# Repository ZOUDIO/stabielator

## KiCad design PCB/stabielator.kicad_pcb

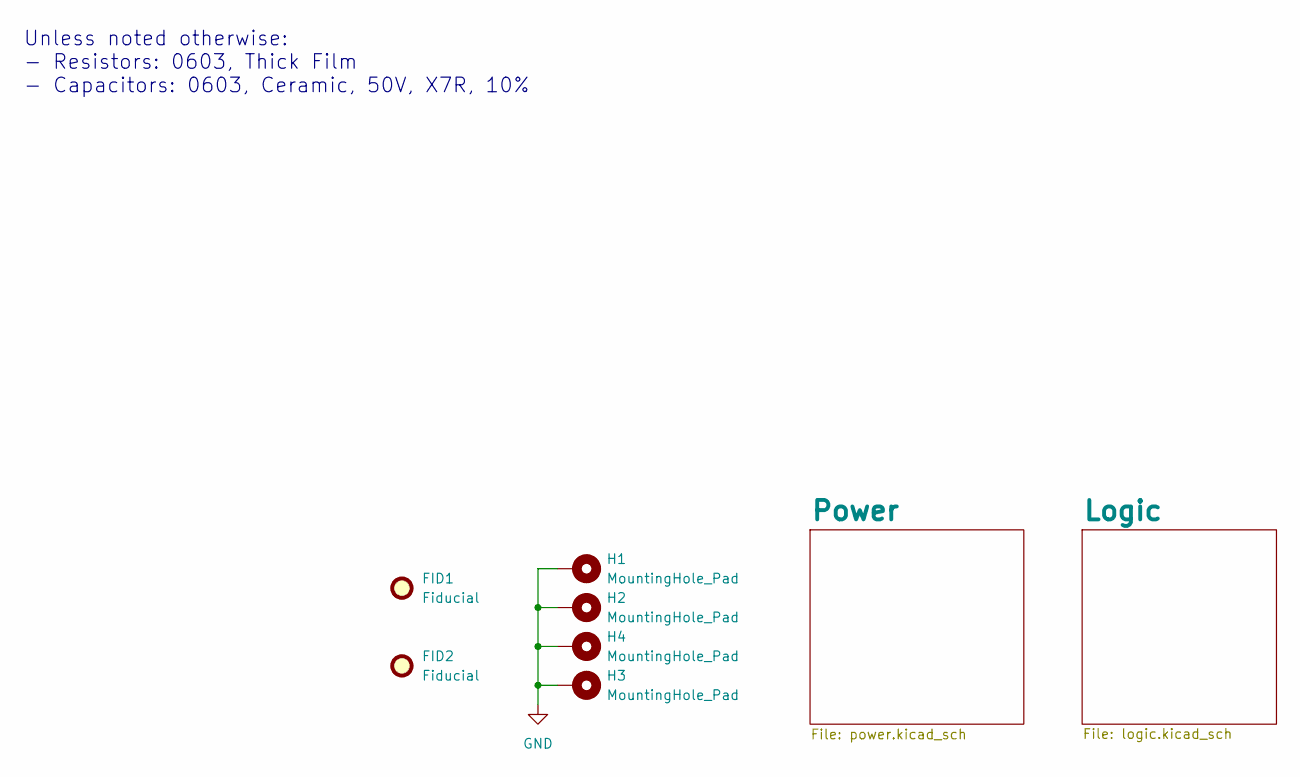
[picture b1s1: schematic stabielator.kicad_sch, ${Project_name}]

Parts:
FID1, FID2: Fiducial; Fiducial_0.5mm_Mask1mm
H1, H2, H3, H4: MountingHole_Pad; MountingHole_2.2mm_M2_Pad_Via; Digikey nvt

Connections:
GND: H1.1 (1_1), H2.1 (1_1), H3.1 (1_1), H4.1 (1_1); also elsewhere on the board

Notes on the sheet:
Unless noted otherwise: - Resistors: 0603, Thick Film - Capacitors: 0603, Ceramic, 50V, X7R, 10%

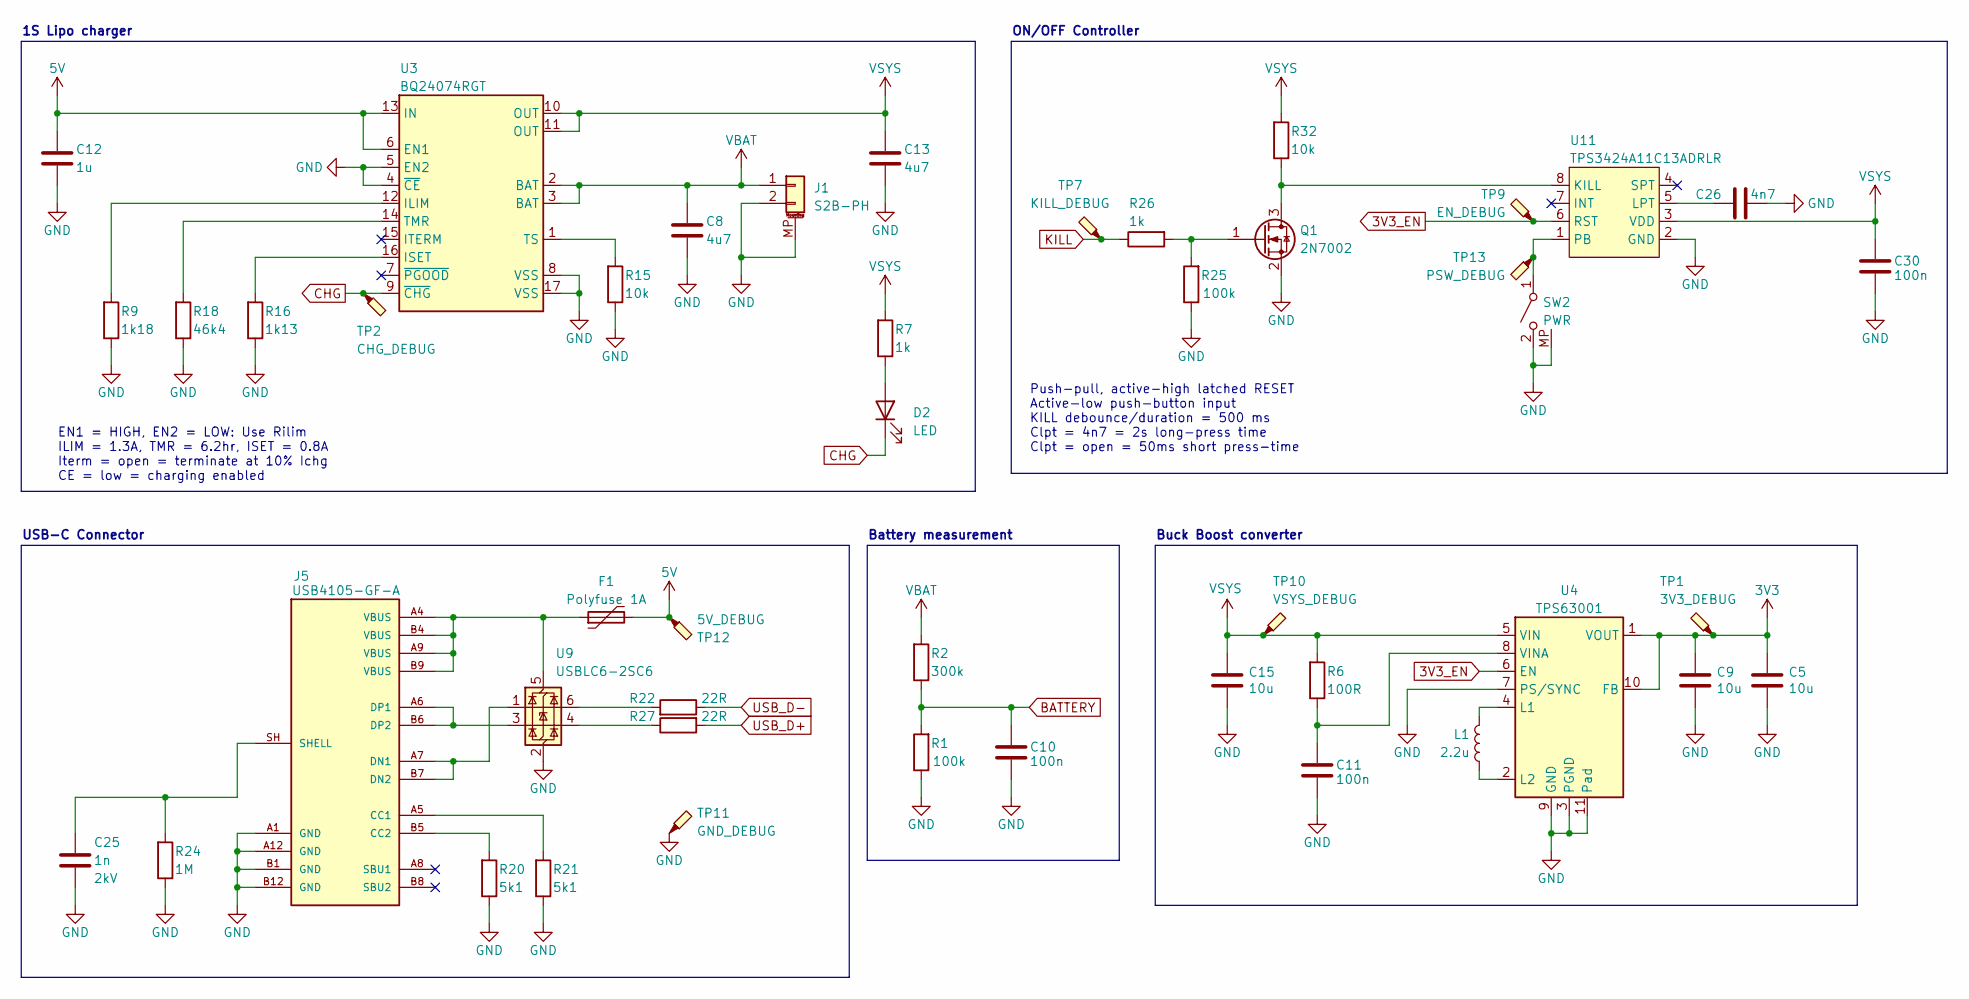
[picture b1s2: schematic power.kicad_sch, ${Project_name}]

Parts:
C5, C9, C15: 10u; C_1206_3216Metric; Partnumber CGA5L1X7R1C106K160AC; Digikey 445-12902-1-ND
C8, C13: 4u7; C_0805_2012Metric; Partnumber GRM21BR71C475KE51L; Digikey 490-14466-1-ND
C10, C11, C30: 100n; C_0603_1608Metric; Partnumber C0603C104K5RACTU; Digikey 399-C0603C104K5RACTUCT-ND
C12: 1u; C_0805_2012Metric; Partnumber GRM21BR71C105KA01L; Digikey 490-1691-1-ND
C25: 1n; C_1206_3216Metric; Voltage 2kV; Partnumber C1206C102KGRACTU; Digikey 399-C1206C102KGRACTUCT-ND
C26: 4n7; C_0603_1608Metric; Partnumber C1608X7R1H472K080AE; Digikey 445-173690-1-ND
D2: LED; LED_0603_1608Metric; Partnumber 150060RS55040; Digikey 732-12015-1-ND
F1: Polyfuse 1A; Fuse_0805_2012Metric; Partnumber 0ZCK0100FF2E; Digikey 5923-0ZCK0100FF2ECT-ND
J1: S2B-PH; JST_PH_S2B-PH-SM4-TB_1x02-1MP_P2.00mm_Horizontal; Partnumber S2B-PH-SM4-TB; Digikey 455-S2B-PH-SM4-TBCT-ND
J5: USB4105-GF-A; USB_C_Receptacle_Palconn_UTC16-G; Partnumber USB4105-GF-A; Digikey 2073-USB4105-GF-ACT-ND
L1: 2.2u; L_Bourns-SRN4018; Partnumber SRN4018-2R2M; Digikey SRN4018-2R2MCT-ND
Q1: 2N7002; SOT-23; Partnumber 2N7002; Digikey 2N7002NCT-ND
R1, R25: 100k; R_0603_1608Metric; Partnumber RC0603FR-07100KL; Digikey 311-100KHRCT-ND
R2: 300k; R_0603_1608Metric; Partnumber RC0603FR-07300KL; Digikey 311-300KHRTR-ND
R6: 100R; R_0603_1608Metric; Partnumber RC0603FR-07100RL; Digikey 311-100HRCT-ND
R7, R26: 1k; R_0603_1608Metric; Partnumber RC0603FR-071KL; Digikey 311-1.00KHRCT-ND
R9: 1k18; R_0603_1608Metric; Partnumber RC0603FR-071K18L; Digikey 311-1.18KHRCT-ND
R15, R32: 10k; R_0603_1608Metric; Partnumber RC0603FR-0710KL; Digikey 311-10.0KHRCT-ND
R16: 1k13; R_0603_1608Metric; Partnumber RC0603FR-071K13L; Digikey 311-1.13KHRCT-ND
R18: 46k4; R_0603_1608Metric; Partnumber RC0603FR-0746K4L; Digikey 311-46.4KHRCT-ND
R20, R21: 5k1; R_0603_1608Metric; Partnumber RC0603FR-075K1L; Digikey 311-5.10KHRTR-ND
R22, R27: 22R; R_0603_1608Metric; Partnumber RC0603FR-0722RL; Digikey 311-22.0HRTR-ND
R24: 1M; R_0603_1608Metric; Partnumber RC0603FR-071ML; Digikey 311-1.00MHRCT-ND
SW2: PWR; SW_Push_1P1T-MP_NO_Horizontal_Alps_SKRTLAE010; Partnumber SKRTLAE010; Digikey 4809-SKRTLAE010CT-ND
TP1: 3V3_DEBUG; TestPoint_Pad_D1.0mm; Digikey nvt
TP2: CHG_DEBUG; TestPoint_Pad_D1.0mm; Digikey nvt
TP7: KILL_DEBUG; TestPoint_Pad_D1.0mm; Digikey nvt
TP9: EN_DEBUG; TestPoint_Pad_D1.0mm; Digikey nvt
TP10: VSYS_DEBUG; TestPoint_Pad_D1.0mm; Digikey nvt
TP11: GND_DEBUG; TestPoint_Pad_D1.0mm; Digikey nvt
TP12: 5V_DEBUG; TestPoint_Pad_D1.0mm; Digikey nvt
TP13: PSW_DEBUG; TestPoint_Pad_D1.0mm; Digikey nvt
U3: BQ24074RGT; VQFN-16-1EP_3x3mm_P0.5mm_EP1.6x1.6mm_ThermalVias; Partnumber BQ24074RGTR; Digikey 296-38873-1-ND
U4: TPS63001; Texas_DRC0010J_ThermalVias; Partnumber TPS63001DRCR; Digikey 296-19643-1-ND
U9: USBLC6-2SC6; SOT-23-6; Partnumber USBLC6-2SC6; Digikey 497-5235-2-ND
U11: TPS3424A11C13ADRLR; SOT-583-8; Partnumber TPS3424A11C13ADRLR; Digikey 296-TPS3424A11C13ADRLRCT-ND

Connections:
3V3: C5.1, C9.1, TP1.1 (1_1), U4.1 (VOUT), U4.10 (FB); also elsewhere on the board
3V3_EN: TP9.1 (1_1), U4.6 (EN), U11.6 (RST)
5V: C12.1, F1.2, TP12.1 (1_1), U3.6 (EN1), U3.13 (IN)
BATTERY: C10.1, R1.1, R2.2; also elsewhere on the board
CHG: D2.1 (K), TP2.1 (1_1), U3.9 (~CHG)
GND: C5.2, C8.2, C9.2, C10.2, C11.2, C12.2, C13.2, C15.2, C25.2, C26.2, C30.2, J1.2, J1.MP (MountPin), J5.A1 (GND), J5.A12 (GND), J5.B1 (GND), J5.B12 (GND), Q1.2 (S), R1.2, R9.2, R15.2, R16.2, R18.2, R20.2, R21.2, R24.2, R25.2, SW2.2 (B), SW2.MP, TP11.1 (1_1), U3.4 (~CE), U3.5 (EN2), U3.8 (VSS), U3.17 (VSS), U4.3 (PGND), U4.7 (PS/SYNC), U4.9 (GND), U4.11 (PGND), U9.2 (GND), U11.2 (GND); also elsewhere on the board
KILL: R26.2, TP7.1 (1_1); also elsewhere on the board
unnamed: D2.2 (A), R7.2
unnamed: J5.A5 (CC1), R21.1
unnamed: J5.B5 (CC2), R20.1
unnamed: J5.A7 (DN1), J5.B7 (DN2), U9.1 (I/O1)
unnamed: J5.A6 (DP1), J5.B6 (DP2), U9.3 (I/O2)
unnamed: C25.1, J5.SH (SHELL), R24.1
unnamed: Q1.3 (D), R32.2, U11.8 (KILL)
unnamed: Q1.1 (G), R25.1, R26.1
unnamed: R22.1, U9.6 (I/O1)
unnamed: R27.2, U9.4 (I/O2)
unnamed: SW2.1 (A), TP13.1 (1_1), U11.1 (PB)
unnamed: R9.1, U3.12 (ILIM)
unnamed: R16.1, U3.16 (ISET)
unnamed: R18.1, U3.14 (TMR)
unnamed: R15.1, U3.1 (TS)
unnamed: L1.1, U4.4 (L1)
unnamed: L1.2, U4.2 (L2)
unnamed: C11.1, R6.2, U4.8 (VINA)
unnamed: F1.1, J5.A4 (VBUS), J5.A9 (VBUS), J5.B4 (VBUS), J5.B9 (VBUS), U9.5 (VBUS)
unnamed: C26.1, U11.5 (LPT)
USB_D+: R27.1; also elsewhere on the board
USB_D-: R22.2; also elsewhere on the board
VBAT: C8.1, J1.1, R2.1, U3.2 (BAT), U3.3 (BAT)
VSYS: C13.1, C15.1, C30.1, R6.1, R7.1, R32.1, TP10.1 (1_1), U3.10 (OUT), U3.11 (OUT), U4.5 (VIN), U11.3 (VDD)

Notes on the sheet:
1S Lipo charger
USB-C Connector
Buck Boost converter
Push-pull, active-high latched RESET Active-low push-button input KILL debounce/duration = 500 ms Clpt = 4n7 = 2s long-press time Clpt = open = 50ms short press-time
EN1 = HIGH, EN2 = LOW: Use Rilim ILIM = 1.3A, TMR = 6.2hr, ISET = 0.8A Iterm = open = terminate at 10% Ichg CE = low = charging enabled
Battery measurement
ON/OFF Controller

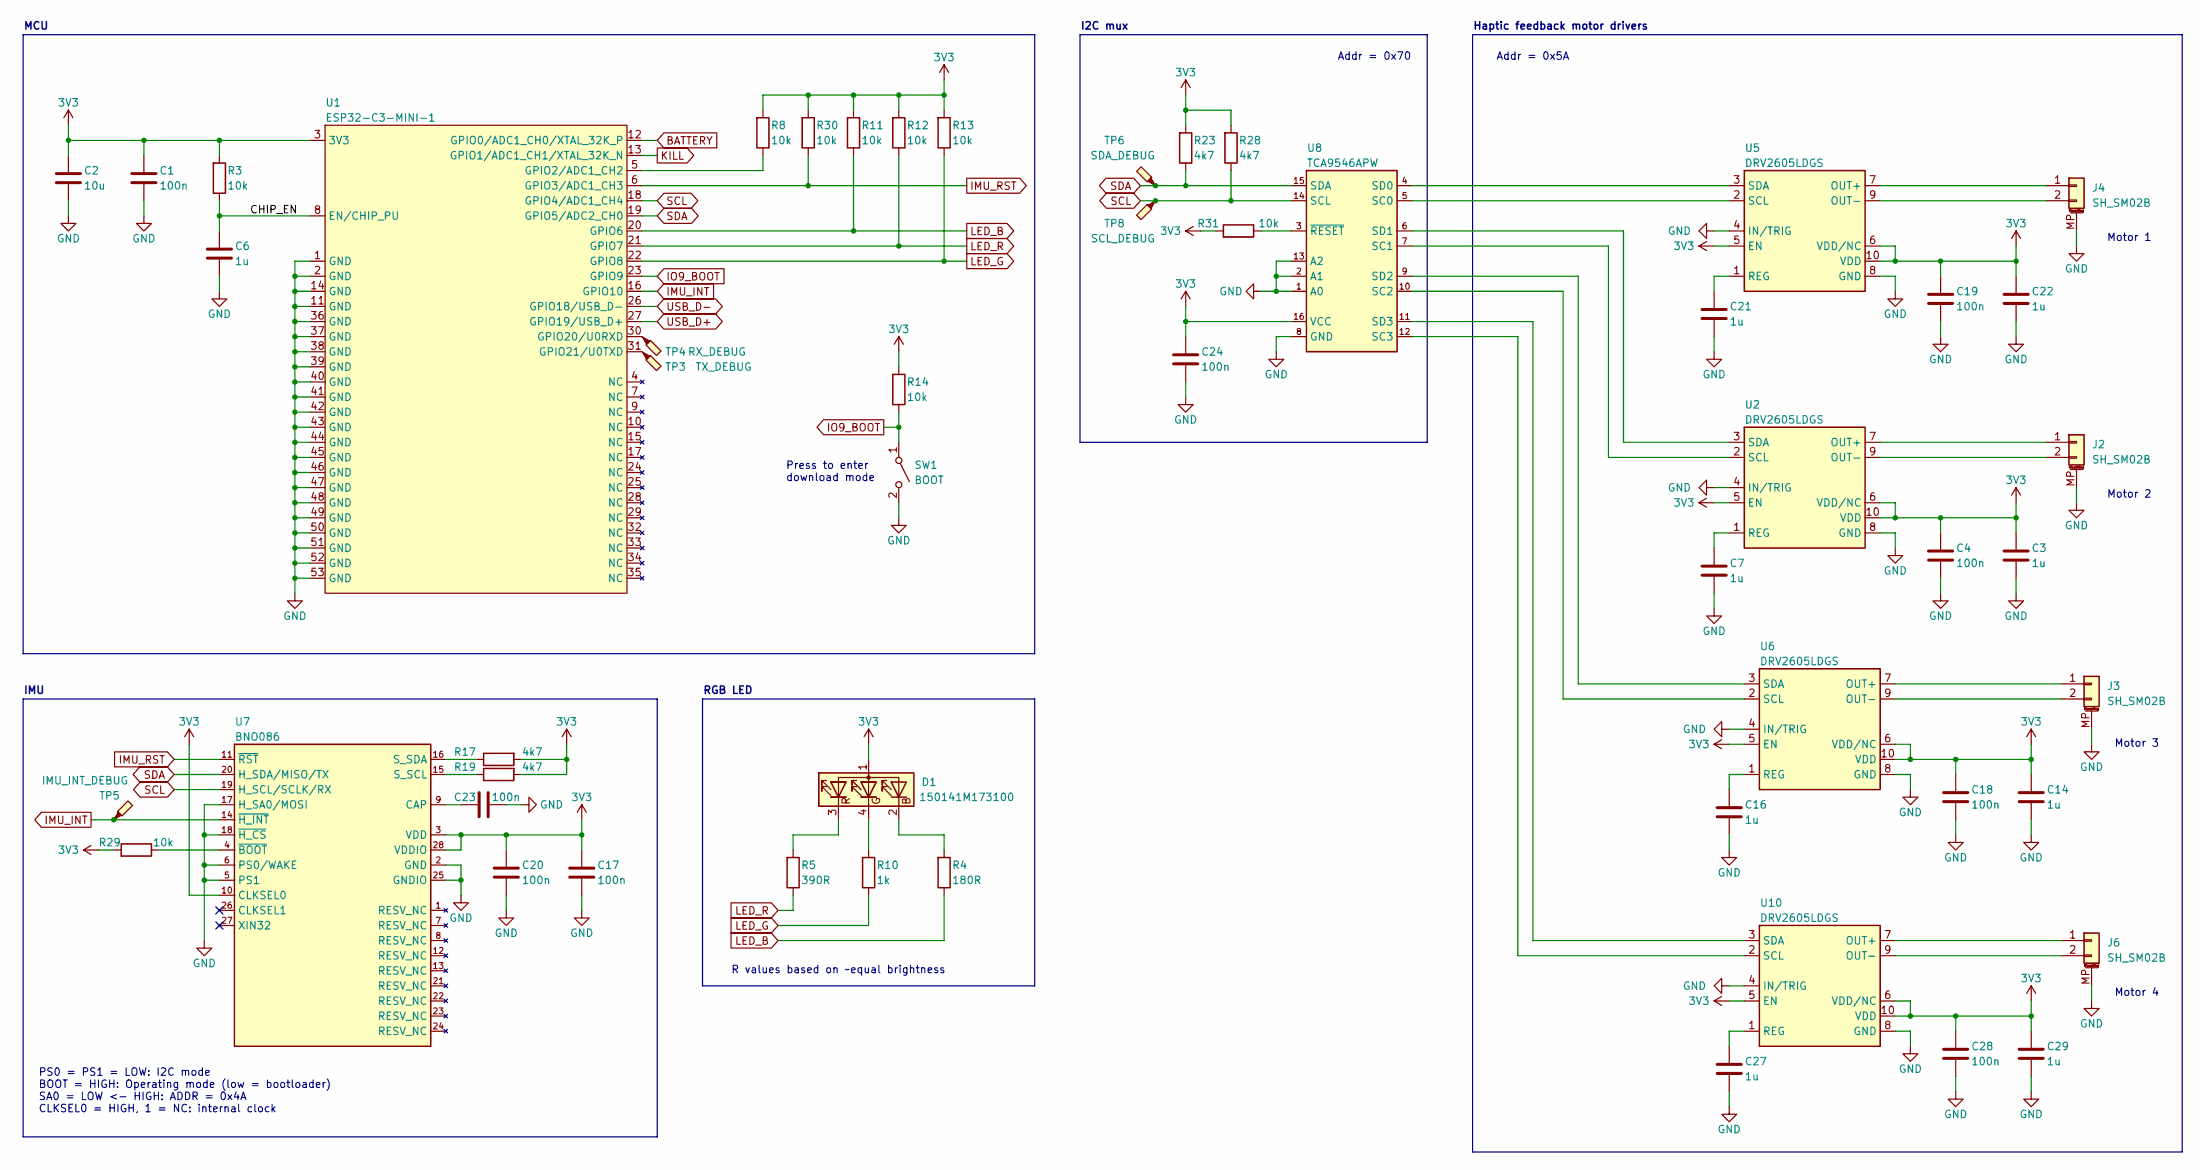
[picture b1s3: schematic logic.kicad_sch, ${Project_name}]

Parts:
C1, C4, C17, C18, C19, C20, C23, C24, C28: 100n; C_0603_1608Metric; Partnumber C0603C104K5RACTU; Digikey 399-C0603C104K5RACTUCT-ND
C2: 10u; C_0805_2012Metric; Partnumber CL21B106KOQNNNE; Digikey 1276-2872-1-ND
C3, C6, C7, C14, C16, C21, C22, C27, C29: 1u; C_0603_1608Metric; Partnumber C1608X7R1C105K080AC; Digikey 445-1604-1-ND
D1: 150141M173100; LED_RGB_Wuerth-PLCC4_3.2x2.8mm_150141M173100; Partnumber 150141M173100; Digikey 732-4998-1-ND
J2, J3, J4, J6: SH_SM02B; JST_SH_SM02B-SRSS-TB_1x02-1MP_P1.00mm_Horizontal; Partnumber SM02B-SRSS-TB; Digikey 455-SM02B-SRSS-TBCT-ND
R3, R8, R11, R12, R13, R14, R29, R30, R31: 10k; R_0603_1608Metric; Partnumber RC0603FR-0710KL; Digikey 311-10.0KHRCT-ND
R4: 180R; R_0603_1608Metric; Partnumber RC0603FR-07180RL; Digikey 311-180HRCT-ND
R5: 390R; R_0603_1608Metric; Partnumber RC0603FR-07390RL; Digikey 311-390HRCT-ND
R10: 1k; R_0603_1608Metric; Partnumber RC0603FR-071KL; Digikey 311-1.00KHRCT-ND
R17, R19, R23, R28: 4k7; R_0603_1608Metric; Partnumber RC0603FR-074K7L; Digikey 311-4.70KHRCT-ND
SW1: BOOT; SW_SPST_B3U-1000P; Partnumber B3U-1000P; Digikey SW1020CT-ND
TP3: TX_DEBUG; TestPoint_Pad_D1.0mm; Digikey nvt
TP4: RX_DEBUG; TestPoint_Pad_D1.0mm; Digikey nvt
TP5: IMU_INT_DEBUG; TestPoint_Pad_D1.0mm; Digikey nvt
TP6: SDA_DEBUG; TestPoint_Pad_D1.0mm; Digikey nvt
TP8: SCL_DEBUG; TestPoint_Pad_D1.0mm; Digikey nvt
U1: ESP32-C3-MINI-1; Partnumber ESP32-C3-MINI-1-N4; Digikey 5407-ESP32-C3-MINI-1-N4CT-ND
U2, U5, U6, U10: DRV2605LDGS; TSSOP-10_3x3mm_P0.5mm; Partnumber DRV2605LDGSR; Digikey 296-40032-1-ND
U7: BNO086; LGA-28; Partnumber BNO086; Digikey 1888-BNO086CT-ND
U8: TCA9546APW; TSSOP-16_4.4x5mm_P0.65mm; Partnumber TCA9546APWR; Digikey 4518-TCA9546APWRCT-ND

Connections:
3V3: C1.1, C2.1, C3.1, C4.1, C14.1, C17.1, C18.1, C19.1, C20.1, C22.1, C24.1, C28.1, C29.1, D1.1 (A), R3.1, R8.1, R11.1, R12.1, R13.1, R14.1, R17.1, R19.1, R23.1, R28.1, R29.1, R30.1, R31.1, U1.3 (3V3), U2.5 (EN), U2.6 (VDD/NC), U2.10 (VDD), U5.5 (EN), U5.6 (VDD/NC), U5.10 (VDD), U6.5 (EN), U6.6 (VDD/NC), U6.10 (VDD), U7.3 (VDD), U7.10 (CLKSEL0), U7.28 (VDDIO), U8.16 (VCC), U10.5 (EN), U10.6 (VDD/NC), U10.10 (VDD); also elsewhere on the board
/Logic/CHIP_EN: C6.1, R3.2, U1.8 (EN/CHIP_PU)
BATTERY: U1.12 (GPIO0/ADC1_CH0/XTAL_32K_P); also elsewhere on the board
GND: C1.2, C2.2, C3.2, C4.2, C6.2, C7.2, C14.2, C16.2, C17.2, C18.2, C19.2, C20.2, C21.2, C22.2, C23.1, C24.2, C27.2, C28.2, C29.2, J2.MP (MountPin), J3.MP (MountPin), J4.MP (MountPin), J6.MP (MountPin), SW1.2 (B), U1.1 (GND), U1.2 (GND), U1.11 (GND), U1.14 (GND), U1.36 (GND), U1.37 (GND), U1.38 (GND), U1.39 (GND), U1.40 (GND), U1.41 (GND), U1.42 (GND), U1.43 (GND), U1.44 (GND), U1.45 (GND), U1.46 (GND), U1.47 (GND), U1.48 (GND), U1.49 (GND), U1.50 (GND), U1.51 (GND), U1.52 (GND), U1.53 (GND), U2.4 (IN/TRIG), U2.8 (GND), U5.4 (IN/TRIG), U5.8 (GND), U6.4 (IN/TRIG), U6.8 (GND), U7.2 (GND), U7.5 (PS1), U7.6 (PS0/WAKE), U7.17 (H_SA0/MOSI), U7.18 (~H_CS), U7.25 (GNDIO), U8.1 (A0), U8.2 (A1), U8.8 (GND), U8.13 (A2), U10.4 (IN/TRIG), U10.8 (GND); also elsewhere on the board
IMU_INT: TP5.1 (1_1), U1.16 (GPIO10), U7.14 (~H_INT)
IMU_RST: R30.2, U1.6 (GPIO3/ADC1_CH3), U7.11 (~RST)
IO9_BOOT: R14.2, SW1.1 (A), U1.23 (GPIO9)
KILL: U1.13 (GPIO1/ADC1_CH1/XTAL_32K_N); also elsewhere on the board
LED_B: R4.2, R11.2, U1.20 (GPIO6)
LED_G: R10.2, R13.2, U1.22 (GPIO8)
LED_R: R5.2, R12.2, U1.21 (GPIO7)
unnamed: D1.2 (BK), R4.1
unnamed: D1.4 (GK), R10.1
unnamed: D1.3 (RK), R5.1
unnamed: J2.1, U2.7 (OUT+)
unnamed: J2.2, U2.9 (OUT-)
unnamed: J3.1, U6.7 (OUT+)
unnamed: J3.2, U6.9 (OUT-)
unnamed: J4.1, U5.7 (OUT+)
unnamed: J4.2, U5.9 (OUT-)
unnamed: J6.1, U10.7 (OUT+)
unnamed: J6.2, U10.9 (OUT-)
unnamed: R8.2, U1.5 (GPIO2/ADC1_CH2)
unnamed: TP4.1 (1_1), U1.30 (GPIO20/U0RXD)
unnamed: TP3.1 (1_1), U1.31 (GPIO21/U0TXD)
unnamed: C7.1, U2.1 (REG)
unnamed: U2.2 (SCL), U8.7 (SC1)
unnamed: U2.3 (SDA), U8.6 (SD1)
unnamed: C21.1, U5.1 (REG)
unnamed: U5.2 (SCL), U8.5 (SC0)
unnamed: U5.3 (SDA), U8.4 (SD0)
unnamed: C16.1, U6.1 (REG)
unnamed: U6.2 (SCL), U8.10 (SC2)
unnamed: U6.3 (SDA), U8.9 (SD2)
unnamed: C23.2, U7.9 (CAP)
unnamed: R19.2, U7.15 (S_SCL)
unnamed: R17.2, U7.16 (S_SDA)
unnamed: R29.2, U7.4 (~BOOT)
unnamed: R31.2, U8.3 (~RESET)
unnamed: C27.1, U10.1 (REG)
unnamed: U8.12 (SC3), U10.2 (SCL)
unnamed: U8.11 (SD3), U10.3 (SDA)
SCL: R28.2, TP8.1 (1_1), U1.18 (GPIO4/ADC1_CH4), U7.19 (H_SCL/SCLK/RX), U8.14 (SCL)
SDA: R23.2, TP6.1 (1_1), U1.19 (GPIO5/ADC2_CH0), U7.20 (H_SDA/MISO/TX), U8.15 (SDA)
USB_D+: U1.27 (GPIO19/USB_D+); also elsewhere on the board
USB_D-: U1.26 (GPIO18/USB_D-); also elsewhere on the board

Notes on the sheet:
I2C mux
IMU
MCU
Haptic feedback motor drivers
Addr = 0x70
Motor 3
PS0 = PS1 = LOW: I2C mode BOOT = HIGH: Operating mode (low = bootloader) SA0 = LOW <- HIGH: ADDR = 0x4A CLKSEL0 = HIGH, 1 = NC: internal clock
RGB LED
Motor 2
Press to enter download mode
R values based on ~equal brightness
Addr = 0x5A
Motor 1
Motor 4

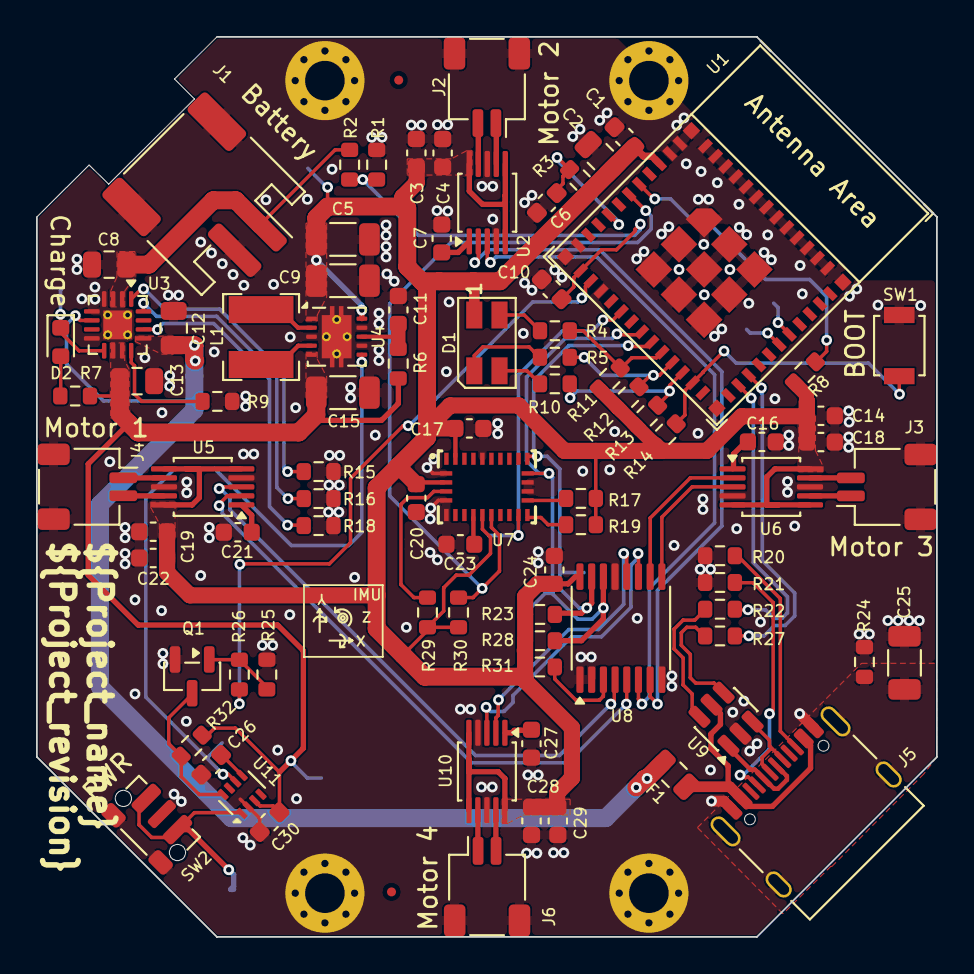
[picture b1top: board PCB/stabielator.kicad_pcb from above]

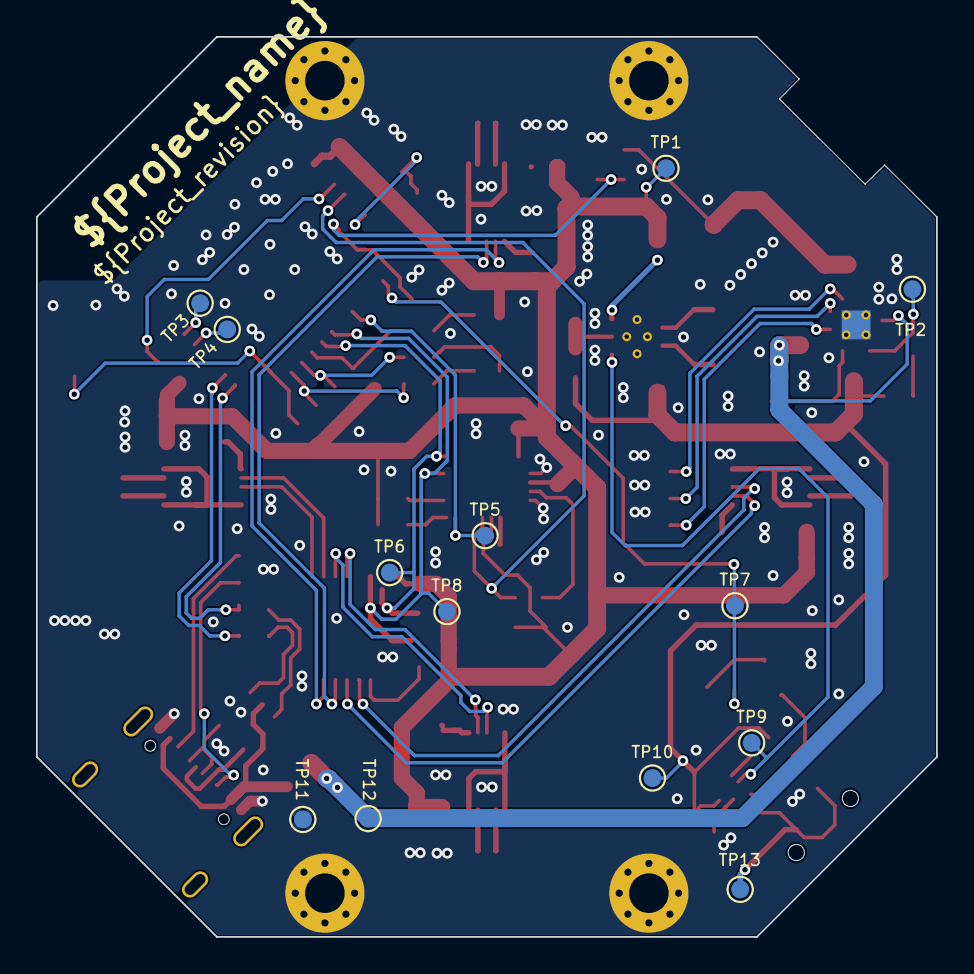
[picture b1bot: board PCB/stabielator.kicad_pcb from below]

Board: 4 copper layers, 50.0 x 50.0 mm, 106 parts (13 on the bottom side), 71 nets.

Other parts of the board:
SYM1: IMU_XYZ_Orientation

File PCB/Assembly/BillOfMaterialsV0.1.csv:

"Reference","Qty","Value","Footprint","Digikey"
"C1,C4,C10,C11,C17,C18,C19,C20,C23,C24,C28,C30","12","100n","Capacitor_SMD:C_0603_1608Metric","399-C0603C104K5RACTUCT-ND"
"C2","1","10u","Capacitor_SMD:C_0805_2012Metric","1276-2872-1-ND"
"C3,C6,C7,C14,C16,C21,C22,C27,C29","9","1u","Capacitor_SMD:C_0603_1608Metric","445-1604-1-ND"
"C5,C9,C15","3","10u","Capacitor_SMD:C_1206_3216Metric","445-12902-1-ND"
"C8,C13","2","4u7","Capacitor_SMD:C_0805_2012Metric","490-14466-1-ND"
"C12","1","1u","Capacitor_SMD:C_0805_2012Metric","490-1691-1-ND"
"C25","1","1n","Capacitor_SMD:C_1206_3216Metric","399-C1206C102KGRACTUCT-ND"
"C26","1","4n7","Capacitor_SMD:C_0603_1608Metric","445-173690-1-ND"
"D1","1","150141M173100","LED_SMD:LED_RGB_Wuerth-PLCC4_3.2x2.8mm_150141M173100","732-4998-1-ND"
"D2","1","LED","LED_SMD:LED_0603_1608Metric","732-12015-1-ND"
"F1","1","Polyfuse 1A","Fuse:Fuse_0805_2012Metric","5923-0ZCK0100FF2ECT-ND"
"J1","1","S2B-PH","Connector_JST:JST_PH_S2B-PH-SM4-TB_1x02-1MP_P2.00mm_Horizontal","455-S2B-PH-SM4-TBCT-ND"
"J2,J3,J4,J6","4","SH_SM02B","Connector_JST:JST_SH_SM02B-SRSS-TB_1x02-1MP_P1.00mm_Horizontal","455-SM02B-SRSS-TBCT-ND"
"J5","1","USB4105-GF-A","Connector_USB:USB_C_Receptacle_Palconn_UTC16-G","2073-USB4105-GF-ACT-ND"
"L1","1","2.2u","Inductor_SMD:L_Bourns-SRN4018","SRN4018-2R2MCT-ND"
"Q1","1","2N7002","Package_TO_SOT_SMD:SOT-23","2N7002NCT-ND"
"R1","1","100k 0.1%","Resistor_SMD:R_0603_1608Metric","YAG1235CT-ND"
"R2","1","300k 0.1%","Resistor_SMD:R_0603_1608Metric","YAG1627CT-ND"
"R3,R8,R11,R12,R13,R14,R15,R29,R30,R31,R32","11","10k","Resistor_SMD:R_0603_1608Metric","311-10.0KHRCT-ND"
"R4","1","180R","Resistor_SMD:R_0603_1608Metric","311-180HRCT-ND"
"R5","1","390R","Resistor_SMD:R_0603_1608Metric","311-390HRCT-ND"
"R6","1","100R","Resistor_SMD:R_0603_1608Metric","311-100HRCT-ND"
"R7,R10,R26","3","1k","Resistor_SMD:R_0603_1608Metric","311-1.00KHRCT-ND"
"R9","1","1k18","Resistor_SMD:R_0603_1608Metric","311-1.18KHRCT-ND"
"R16","1","1k13","Resistor_SMD:R_0603_1608Metric","311-1.13KHRCT-ND"
"R17,R19,R23,R28","4","4k7","Resistor_SMD:R_0603_1608Metric","311-4.70KHRCT-ND"
"R18","1","46k4","Resistor_SMD:R_0603_1608Metric","311-46.4KHRCT-ND"
"R20,R21","2","5k1","Resistor_SMD:R_0603_1608Metric","YAG3621CT-ND"
"R22,R27","2","22R","Resistor_SMD:R_0603_1608Metric","YAG3581CT-ND"
"R24","1","1M","Resistor_SMD:R_0603_1608Metric","311-1.00MHRCT-ND"
"R25","1","100k","Resistor_SMD:R_0603_1608Metric","311-100KHRCT-ND"
"SW1","1","BOOT","Button_Switch_SMD:SW_SPST_B3U-1000P","SW1020CT-ND"
"SW2","1","PWR","Button_Switch_SMD:SW_Push_1P1T-MP_NO_Horizontal_Alps_SKRTLAE010","4809-SKRTLAE010CT-ND"
"U1","1","ESP32-C3-MINI-1","PCM_Espressif:ESP32-C3-MINI-1","5407-ESP32-C3-MINI-1-N4CT-ND"
"U2,U5,U6,U10","4","DRV2605LDGS","Package_SO:TSSOP-10_3x3mm_P0.5mm","296-40032-1-ND"
"U3","1","BQ24074RGT","Package_DFN_QFN:VQFN-16-1EP_3x3mm_P0.5mm_EP1.6x1.6mm_ThermalVias","296-38873-1-ND"
"U4","1","TPS63001","Package_SON:Texas_DRC0010J_ThermalVias","296-19643-1-ND"
"U7","1","BNO086","stabielator:LGA-28","1888-BNO086CT-ND"
"U8","1","TCA9546APW","Package_SO:TSSOP-16_4.4x5mm_P0.65mm","4518-TCA9546APWRCT-ND"
"U9","1","USBLC6-2SC6","Package_TO_SOT_SMD:SOT-23-6","5399-USBLC6-2SC6CT-ND"
"U11","1","TPS3424A11C13ADRLR","Package_TO_SOT_SMD:SOT-583-8","296-TPS3424A11C13ADRLRCT-ND"

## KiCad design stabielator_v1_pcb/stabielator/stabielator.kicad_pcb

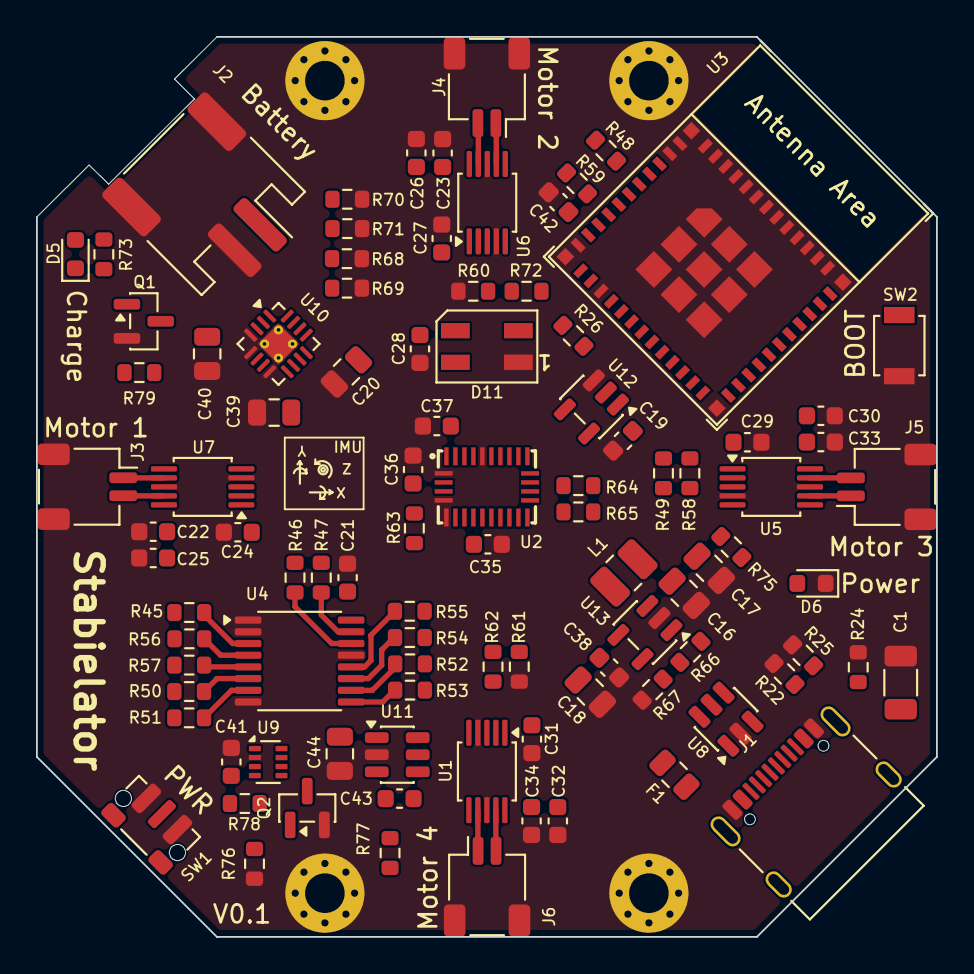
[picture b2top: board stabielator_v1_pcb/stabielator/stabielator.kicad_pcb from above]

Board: 2 copper layers, 50.0 x 50.0 mm, 100 parts (0 on the bottom side), 68 nets.

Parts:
C1: 1n-2kV; C_1206_3216Metric
C16, C17, C18: 22uF; C_0805_2012Metric
C19, C21, C22, C23, C28, C33, C34, C35, C36, C37, C38, C41: 100nF; C_0603_1608Metric
C20, C44: 1uF; C_0805_2012Metric
C24, C25, C26, C27, C29, C30, C31, C32: 1uF; C_0603_1608Metric
C39, C40: 4.7uF; C_0805_2012Metric
C42: 1U; C_0603_1608Metric
C43: 1nF; C_0603_1608Metric
D5: LED_R; LED_0603_1608Metric
D6: LED_G; LED_0603_1608Metric
D11: SK6812; LED_SK6812MINI_PLCC4_3.5x3.5mm_P1.75mm
F1: Polyfuse 1A; Fuse_0805_2012Metric
H1, H2, H3, H4: MountingHole_Pad; MountingHole_2.2mm_M2_Pad_Via
J1: USB_C_Receptacle_USB2.0_16P; USB_C_Receptacle_Palconn_UTC16-G
J2: Battery; JST_PH_S2B-PH-SM4-TB_1x02-1MP_P2.00mm_Horizontal
J3: Motor 1; JST_SH_SM02B-SRSS-TB_1x02-1MP_P1.00mm_Horizontal
J4: Motor 2; JST_SH_SM02B-SRSS-TB_1x02-1MP_P1.00mm_Horizontal
J5: Motor 3; JST_SH_SM02B-SRSS-TB_1x02-1MP_P1.00mm_Horizontal
J6: Motor 4; JST_SH_SM02B-SRSS-TB_1x02-1MP_P1.00mm_Horizontal
L1: 2.2uH; L_1008_2520Metric
Q1, Q2: 2N7002; SOT-23
R22, R25: 5k1; R_0603_1608Metric
R24: 1M; R_0603_1608Metric
R26: 330R; R_0603_1608Metric
R45, R48, R49, R58, R59, R60, R61, R62, R63, R71, R72, R78: 10K; R_0603_1608Metric
R46, R47, R50, R51, R52, R53, R54, R55, R56, R57, R64, R65: 4K7; R_0603_1608Metric
R66: 453K; R_0603_1608Metric
R67, R76, R79: 100K; R_0603_1608Metric
R68: 46.4K; R_0603_1608Metric
R69: 1.13K; R_0603_1608Metric
R70: 1.18K; R_0603_1608Metric
R73, R75, R77: 1K; R_0603_1608Metric
SW1: PWR; SW_Push_1P1T-MP_NO_Horizontal_Alps_SKRTLAE010
SW2: BOOT; SW_SPST_B3U-1000P
U1, U5, U6, U7: DRV2605LDGS; TSSOP-10_3x3mm_P0.5mm
U2: LGA-28
U3: ESP32-C3-MINI-1
U4: TCA9546APW; TSSOP-16_4.4x5mm_P0.65mm
U8: USBLC6-2SC6; SOT-23-6
U9: TPS3424A11C13ADRLR; SOT-583-8
U10: BQ24074RGT; VQFN-16-1EP_3x3mm_P0.5mm_EP1.6x1.6mm_ThermalVias
U11: TPS22917DBV; SOT-23-6
U12: 74AHCT1G126; SOT-23-5
U13: TLV62569DBV; SOT-23-5

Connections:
3V3: C16.2, C17.2, C36.2, C37.2, L1.2, R48.1, R49.1, R58.1, R59.1, R63.2, R64.1, R65.1, R66.1, R72.1, R75.1, U2.3 (VDD), U2.10 (CLKSEL0), U2.28 (VDDIO), U3.3 (3V3)
5V: C20.2, F1.2, U10.6 (EN1), U10.13 (IN)
+3.3V: C21.2, R45.1, R46.1, R47.1, U4.16 (VCC)
+BATT: C40.2, J2.1, U10.2 (BAT), U10.3 (BAT)
/CHIP_EN: C42.1, R59.2, U3.8 (EN/CHIP_PU)
BATTERY: R61.1, R62.2, U3.6 (GPIO3/ADC1_CH3)
BATT_VCC: C39.2, C41.1, C44.2, D5.2 (A), R78.1, R79.1, U9.3 (VDD), U10.10 (OUT), U10.11 (OUT), U11.1 (VIN)
CHARGE: Q1.3 (D), R72.2, U3.13 (GPIO1/ADC1_CH1/XTAL_32K_N)
GND: C1.2, C16.1, C17.1, C18.1, C19.1, C20.1, C21.1, C22.2, C23.2, C24.2, C25.2, C26.2, C27.2, C28.2, C29.2, C30.2, C31.2, C32.2, C33.2, C34.2, C35.1, C36.1, C37.1, C38.2, C39.1, C40.1, C41.2, C42.2, C44.1, D6.1 (K), D11.1 (VSS), H1.1 (1_1), H2.1 (1_1), H3.1 (1_1), H4.1 (1_1), J1.A1 (GND), J1.A12 (GND), J1.B1 (GND), J1.B12 (GND), J2.2, J2.MP (MountPin), J3.MP (MountPin), J4.MP (MountPin), J5.MP (MountPin), J6.MP (MountPin), Q1.2 (S), Q2.2 (S), R22.2, R24.2, R25.2, R60.2, R61.2, R67.2, R68.2, R69.2, R70.2, R71.2, R76.1, SW1.1 (A), SW2.1 (A), U1.4 (IN/TRIG), U1.8 (GND), U2.2 (GND), U2.5 (PS1), U2.6 (PS0/WAKE), U2.25 (GNDIO), U3.1 (GND), U3.2 (GND), U3.11 (GND), U3.14 (GND), U3.36 (GND), U3.37 (GND), U3.38 (GND), U3.39 (GND), U3.40 (GND), U3.41 (GND), U3.42 (GND), U3.43 (GND), U3.44 (GND), U3.45 (GND), U3.46 (GND), U3.47 (GND), U3.48 (GND), U3.49 (GND), U3.50 (GND), U3.51 (GND), U3.52 (GND), U3.53 (GND), U4.1 (A0), U4.2 (A1), U4.8 (GND), U4.13 (A2), U5.4 (IN/TRIG), U5.8 (GND), U6.4 (IN/TRIG), U6.8 (GND), U7.4 (IN/TRIG), U7.8 (GND), U8.2 (GND), U9.2 (GND), U10.4 (~CE), U10.5 (EN2), U10.8 (VSS), U10.17 (VSS), U11.2 (GND), U12.3 (GND), U13.2 (GND)
IMU_INT: U2.14 (~H_INT), U3.12 (GPIO0/ADC1_CH0/XTAL_32K_P)
IMU_RST: U2.11 (~RST), U3.21 (GPIO7)
KILL: R77.2, U3.20 (GPIO6)
NEOPIXEL: R60.1, U3.16 (GPIO10), U12.2
unnamed: D5.1 (K), R73.1
unnamed: D6.2 (A), R75.2
unnamed: D11.2 (DIN), R26.2
unnamed: J1.A5 (CC1), R25.1
unnamed: J1.B5 (CC2), R22.1
unnamed: J1.A6 (D+), J1.B6 (D+), U8.3 (I/O2)
unnamed: J1.A7 (D-), J1.B7 (D-), U8.1 (I/O1)
unnamed: C1.1, R24.1
unnamed: J3.1, U7.7 (OUT+)
unnamed: J3.2, U7.9 (OUT-)
unnamed: J4.1, U6.7 (OUT+)
unnamed: J4.2, U6.9 (OUT-)
unnamed: J5.1, U5.7 (OUT+)
unnamed: J5.2, U5.9 (OUT-)
unnamed: J6.1, U1.7 (OUT+)
unnamed: J6.2, U1.9 (OUT-)
unnamed: Q1.1 (G), R73.2, R79.2, U10.9 (~CHG)
unnamed: Q2.3 (D), R78.2, U9.8 (KILL)
unnamed: Q2.1 (G), R76.2, R77.1
unnamed: R26.1, U12.4
unnamed: SW1.2 (B), U9.1 (PB)
unnamed: R58.2, SW2.2 (B), U3.23 (GPIO9)
unnamed: C31.1, U1.1 (REG)
unnamed: R55.2, U1.2 (SCL), U4.12 (SC3)
unnamed: R54.2, U1.3 (SDA), U4.11 (SD3)
unnamed: C35.2, U2.9 (CAP)
unnamed: R65.2, U2.15 (S_SCL)
unnamed: R64.2, U2.16 (S_SDA)
unnamed: R63.1, U2.4 (~BOOT)
unnamed: R48.2, U3.5 (GPIO2/ADC1_CH2)
unnamed: R49.2, U3.22 (GPIO8)
unnamed: R57.2, U4.5 (SC0), U7.2 (SCL)
unnamed: R51.2, U4.7 (SC1), U6.2 (SCL)
unnamed: R52.2, U4.10 (SC2), U5.2 (SCL)
unnamed: R56.2, U4.4 (SD0), U7.3 (SDA)
unnamed: R50.2, U4.6 (SD1), U6.3 (SDA)
unnamed: R53.2, U4.9 (SD2), U5.3 (SDA)
unnamed: R45.2, U4.3 (~RESET)
unnamed: C29.1, U5.1 (REG)
unnamed: C27.1, U6.1 (REG)
unnamed: C24.1, U7.1 (REG)
unnamed: F1.1, J1.A4 (VBUS), J1.A9 (VBUS), J1.B4 (VBUS), J1.B9 (VBUS), U8.5 (VBUS)
unnamed: R70.1, U10.12 (ILIM)
unnamed: R69.1, U10.16 (ISET)
unnamed: R68.1, U10.14 (TMR)
unnamed: R71.1, U10.1 (TS)
unnamed: C43.2, U11.4 (CT)
unnamed: C43.1, U9.6 (RST), U11.3 (ON)
unnamed: R66.2, R67.1, U13.5 (FB)
unnamed: L1.1, U13.3 (SW)
SCL: R46.2, U2.19 (H_SCL/SCLK/RX), U3.18 (GPIO4/ADC1_CH4), U4.14 (SCL)
SDA: R47.2, U2.20 (H_SDA/MISO/TX), U3.19 (GPIO5/ADC2_CH0), U4.15 (SDA)
USB_D+: U3.27 (GPIO19/USB_D+), U8.4 (I/O2)
USB_D-: U3.26 (GPIO18/USB_D-), U8.6 (I/O1)
VCC: C18.2, C19.2, C22.1, C23.1, C25.1, C26.1, C28.1, C30.1, C32.1, C33.1, C34.1, C38.1, D11.3 (VDD), R50.1, R51.1, R52.1, R53.1, R54.1, R55.1, R56.1, R57.1, R62.1, U1.5 (EN), U1.10 (VDD), U5.5 (EN), U5.10 (VDD), U6.5 (EN), U6.10 (VDD), U7.5 (EN), U7.10 (VDD), U11.5 (QOD), U11.6 (VOUT), U12.1, U12.5 (VCC), U13.1 (EN), U13.4 (VIN)

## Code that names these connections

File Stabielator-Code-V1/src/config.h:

/**
 * @file config.h
 * @brief Productieprofielen, hardwarepinnen, tijdslimieten en elektrische motorinstellingen.
 * @date 2026-11-08
 * @author ProtoIoT Wietse Houwers
 * @note Prototype software for evaluation use only.
 */
#pragma once
#include <Arduino.h>

#ifndef STABIELATOR_LRA
#define STABIELATOR_LRA 0
#endif
constexpr bool HAPTIC_IS_LRA = STABIELATOR_LRA != 0;

#define APP_VERSION_TEXT "0.5.2"
constexpr char APP_VERSION[] = APP_VERSION_TEXT;
#if STABIELATOR_LRA
constexpr char OTA_TARGET[] = "stab-c3-lra";
#else
constexpr char OTA_TARGET[] = "stab-c3-erm";
#endif
constexpr char APP_NAME[] = "Stabielator";
constexpr uint32_t SERIAL_BAUD_RATE = 115200;
constexpr uint32_t SERIAL_WAIT_TIMEOUT_MS = 1500;
constexpr size_t SERIAL_COMMAND_BUFFER_SIZE = 128;
constexpr size_t DEVICE_SERIAL_BUFFER_SIZE = 13;
constexpr char APP_PREFERENCES_NAMESPACE[] = "stabielator";

// Pinout uit het Stabielator v0.1.0 schema. USB: GPIO18/19.
constexpr uint8_t I2C_SDA_PIN = 5;
constexpr uint8_t I2C_SCL_PIN = 4;
constexpr uint32_t I2C_CLOCK_HZ = 100000;
constexpr uint8_t IMU_RESET_PIN = 3;
constexpr uint8_t IMU_INT_PIN = 10;
constexpr uint8_t IMU_ADDRESS = 0x4A;
constexpr uint32_t IMU_REPORT_INTERVAL_US = 20000;
constexpr uint32_t IMU_STALE_MS = 250;
constexpr uint8_t RGB_RED_PIN = 7;
constexpr uint8_t RGB_GREEN_PIN = 8;
constexpr uint8_t RGB_BLUE_PIN = 6;
constexpr bool RGB_COMMON_ANODE = true;
constexpr uint8_t BUTTON_PIN = 9;
constexpr uint32_t BUTTON_DEBOUNCE_MS = 35;
constexpr uint32_t WIFI_PAIR_HOLD_MS = 5000;
// 1-cels LiPo via 300k boven / 100k naar GND; GPIO1 HIGH schakelt uit.
constexpr uint8_t BATTERY_PIN = 0;
constexpr uint8_t KILL_PIN = 1;
constexpr float BATTERY_DIVIDER_RATIO = 4.0f;

constexpr uint8_t HAPTIC_MUX_ADDRESS = 0x70; // TCA9546A, vier kanalen
constexpr uint8_t HAPTIC_DRIVER_ADDRESS = 0x5A;
constexpr uint8_t HAPTIC_MOTOR_COUNT = 4;
constexpr uint8_t HAPTIC_CHANNELS[HAPTIC_MOTOR_COUNT] = {0, 1, 2, 3};
constexpr uint32_t HAPTIC_MAX_PULSE_MS = 1000;
constexpr bool HAPTIC_PROFILE_CONFIGURED = true;
constexpr const char* HAPTIC_MOTOR_MODEL = HAPTIC_IS_LRA ? "VLV041235L-L20" : "VZ6DL2B0055211";
// ERM: VZ6DL2B0055211, 3.0 V nominaal, 2.2-3.6 V DC (datasheet p.3-4).
// 0x16 = 141 * 21.18 mV = 2.986 V (genegeerd in ERM open-loop).
// 0x17 = 138 * 21.59 mV = 2.979 V bij volle open-loop RTP-sterkte.
// LRA: VLV041235L-L20, 1.8 Vrms, max 1.85 Vrms sinus, 240 +/-10 Hz (p.4-5).
// TI DRV2605L 8.5.2.1 eq.5: SAMPLE_TIME=300 us, f=240 Hz:
// 0x16 = 69 -> 69 * .02058 / sqrt(1 - .0015*240) = 1.775 Vrms.
// Bij 250 Hz wordt dat 1.796 Vrms. Eq.9: 0x17 = 123 -> 2.610 V piek,
// of 1.846 Vrms sinus-equivalent, onder de gespecificeerde max 1.85 Vrms.
constexpr uint8_t HAPTIC_RATED_VOLTAGE_REGISTER = HAPTIC_IS_LRA ? 0x45 : 0x8D;
constexpr uint8_t HAPTIC_OVERDRIVE_CLAMP_REGISTER = HAPTIC_IS_LRA ? 0x7B : 0x8A;
// LRA: brake factor 2, loop gain 2, initial BEMF gain 2 (auto-cal past dit aan).
constexpr uint8_t HAPTIC_FEEDBACK_REGISTER = HAPTIC_IS_LRA ? 0xAA : 0x36;
// LRA DRIVE_TIME = 16 * 0.1 + 0.5 = 2.1 ms, startschatting ~238 Hz.
constexpr uint8_t HAPTIC_CONTROL1_REGISTER = HAPTIC_IS_LRA ? 0x90 : 0x93;
constexpr uint8_t HAPTIC_CONTROL2_REGISTER = 0xF5; // Signed/bidirectional, sample 300 us.
constexpr uint8_t HAPTIC_CONTROL3_REGISTER = HAPTIC_IS_LRA ? 0x80 : 0xA0;
constexpr uint8_t HAPTIC_CONTROL4_REGISTER = 0x30; // LRA auto-cal: 1000-1200 ms, OTP uit.
constexpr uint32_t HAPTIC_LRA_CALIBRATION_TIMEOUT_MS = 1500;

constexpr char WIFI_AP_NAME_PREFIX[] = "STABIELATOR";
constexpr char WIFI_PORTAL_TITLE[] = "Stabielator v" APP_VERSION_TEXT;
constexpr size_t WIFI_AP_NAME_BUFFER_SIZE = 26;
constexpr size_t WIFI_SSID_MAX_LENGTH = 32;
constexpr size_t WIFI_PASSWORD_MAX_LENGTH = 64;
constexpr char WIFI_AP_PASSWORD[] = "";
constexpr uint32_t WIFI_RECONNECT_INTERVAL_MS = 10000;
constexpr uint16_t WIFI_CONNECT_TIMEOUT_SECONDS = 15;

constexpr uint8_t WIFI_AP_CHANNEL = 1;
constexpr uint32_t WIFI_PORTAL_FALLBACK_MS = 30000;
